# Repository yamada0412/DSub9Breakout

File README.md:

# DSub9Breakout
DSub9Breakout

Ref:https://yamakashi.tech/?p=40

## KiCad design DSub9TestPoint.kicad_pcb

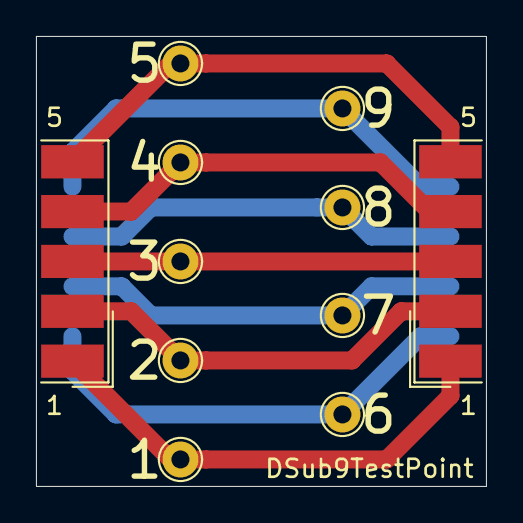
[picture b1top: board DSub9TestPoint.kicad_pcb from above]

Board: 2 copper layers, 25.0 x 25.0 mm, 11 parts (0 on the bottom side), 9 nets.

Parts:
1, 2, 3, 4, 5, 6, 7, 8, 9: TestPoint; TestPoint_THTPad_D2.0mm_Drill1.0mm
J1: DB9_Female; DSUB-9_Female_EdgeMount_P2.77mm
J2: DB9_Male; DSUB-9_Male_EdgeMount_P2.77mm

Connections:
P1: 1.1, J1.1, J2.1
P2: 2.1, J1.2, J2.2
P3: 3.1, J1.3, J2.3
P4: 4.1, J1.4, J2.4
P5: 5.1, J1.5, J2.5
P6: 6.1, J1.6, J2.6
P7: 7.1, J1.7, J2.7
P8: 8.1, J1.8, J2.8
P9: 9.1, J1.9, J2.9

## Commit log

2021-06-13 initial
    initial
